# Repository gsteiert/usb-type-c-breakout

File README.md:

# usb-type-c-breakout
USB Type C Breakout Adapter

This board breaks out a USB Type-C plug to pairs of SMA connectors for each of the super speed pairs, a USB micro B connector for D+/-, and an 8 pin header for the rest of the signals.

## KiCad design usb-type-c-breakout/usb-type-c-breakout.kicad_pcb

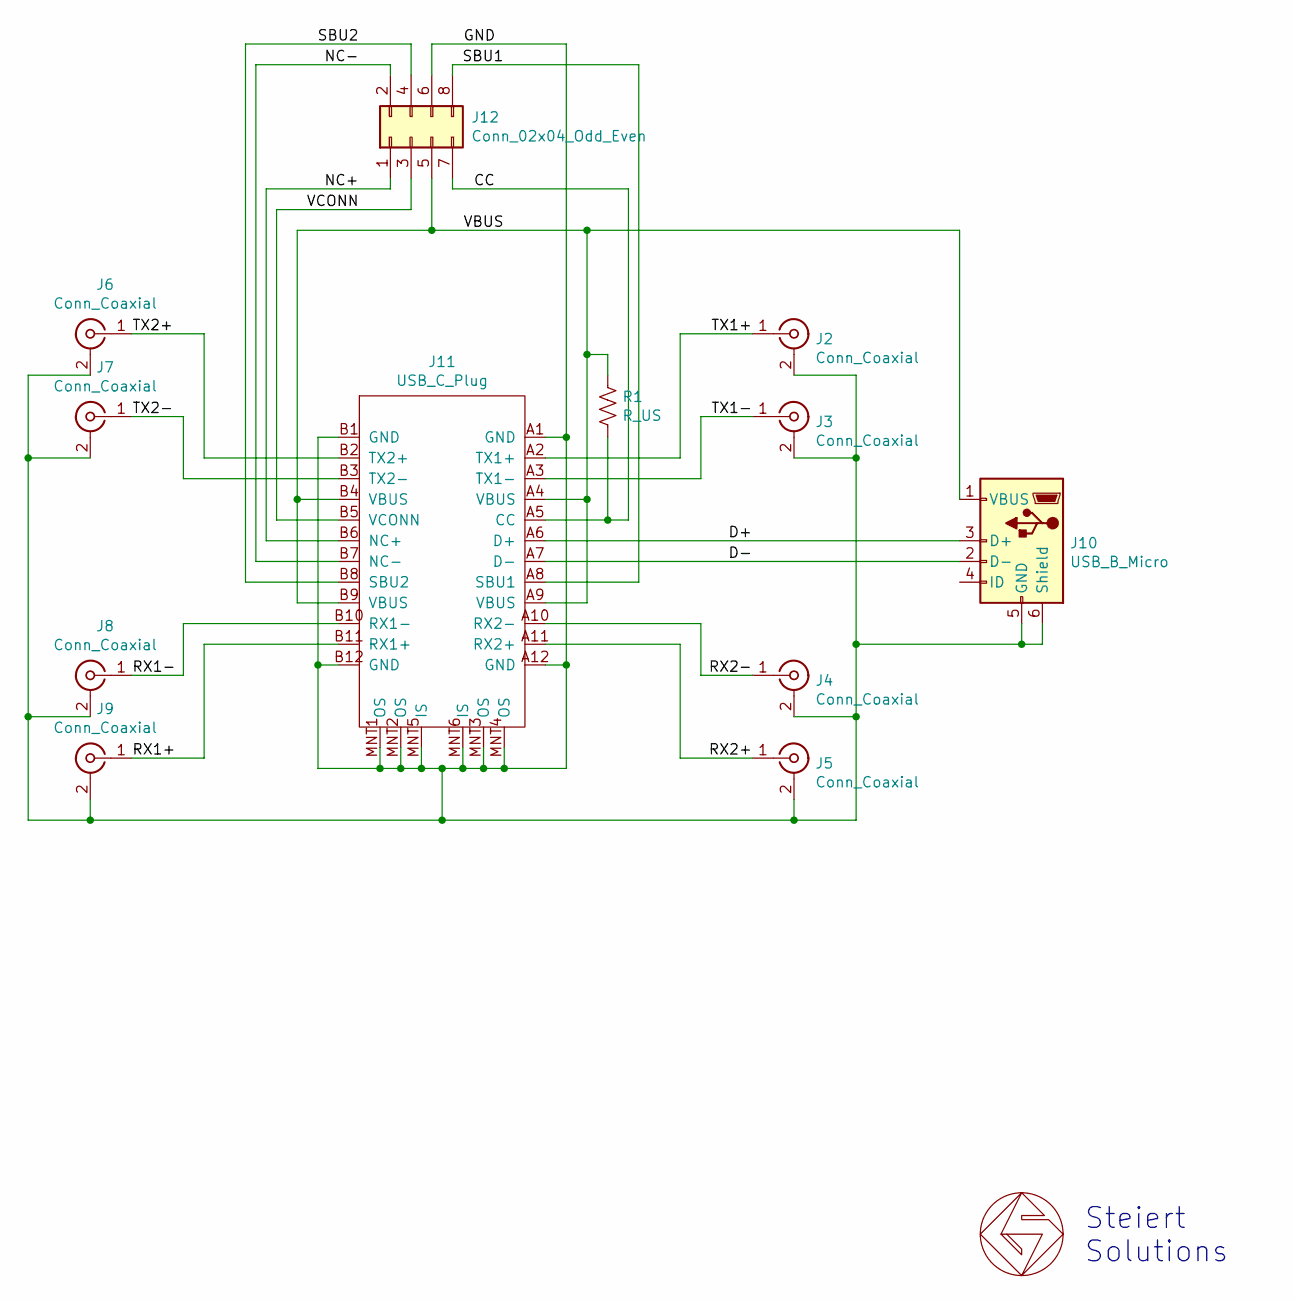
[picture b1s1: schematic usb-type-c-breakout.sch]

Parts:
GS1: GS_logo-custom; gs_logo_200mil
J2, J3, J4, J5, J6, J7, J8, J9: Conn_Coaxial; SMA_Amphenol_132289_EdgeMount; Mouser 223-CON-SMA-EDGE
J10: USB_B_Micro; USB_Micro-B_Wuerth_629105150521; Mouser 710-629105150521
J11: USB_C_Plug; USB_C_Plug_Vertical; Mouser 656-DX07VN24WA2C1568
J12: Conn_02x04_Odd_Even; PinHeader_2x04_P2.54mm_Vertical_SMD; Mouser 649-1012938390801ALF
R1: R_US; R_0603_1608Metric; Mouser 652-CR0603JW-563ELF

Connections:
/CC: J11.A5 (CC), J12.7, R1.2
/D+: J10.3 (D+), J11.A6 (D+)
/D-: J10.2 (D-), J11.A7 (D-)
/GND: J2.2 (Ext), J3.2 (Ext), J4.2 (Ext), J5.2 (Ext), J6.2 (Ext), J7.2 (Ext), J8.2 (Ext), J9.2 (Ext), J10.5 (GND), J10.6 (Shield), J11.A1 (GND), J11.A12 (GND), J11.B1 (GND), J11.B12 (GND), J11.MNT1 (OS), J11.MNT2 (OS), J11.MNT3 (OS), J11.MNT4 (OS), J11.MNT5 (IS), J11.MNT6 (IS), J12.6
/NC+: J11.B6 (NC+), J12.1
/NC-: J11.B7 (NC-), J12.2
/RX1+: J9.1 (In), J11.B11 (RX1+)
/RX1-: J8.1 (In), J11.B10 (RX1-)
/RX2+: J5.1 (In), J11.A11 (RX2+)
/RX2-: J4.1 (In), J11.A10 (RX2-)
/SBU1: J11.A8 (SBU1), J12.8
/SBU2: J11.B8 (SBU2), J12.4
/TX1+: J2.1 (In), J11.A2 (TX1+)
/TX1-: J3.1 (In), J11.A3 (TX1-)
/TX2+: J6.1 (In), J11.B2 (TX2+)
/TX2-: J7.1 (In), J11.B3 (TX2-)
/VBUS: J10.1 (VBUS), J11.A4 (VBUS), J11.A9 (VBUS), J11.B4 (VBUS), J11.B9 (VBUS), J12.5, R1.1
/VCONN: J11.B5 (VCONN), J12.3

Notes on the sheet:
Steiert Solutions

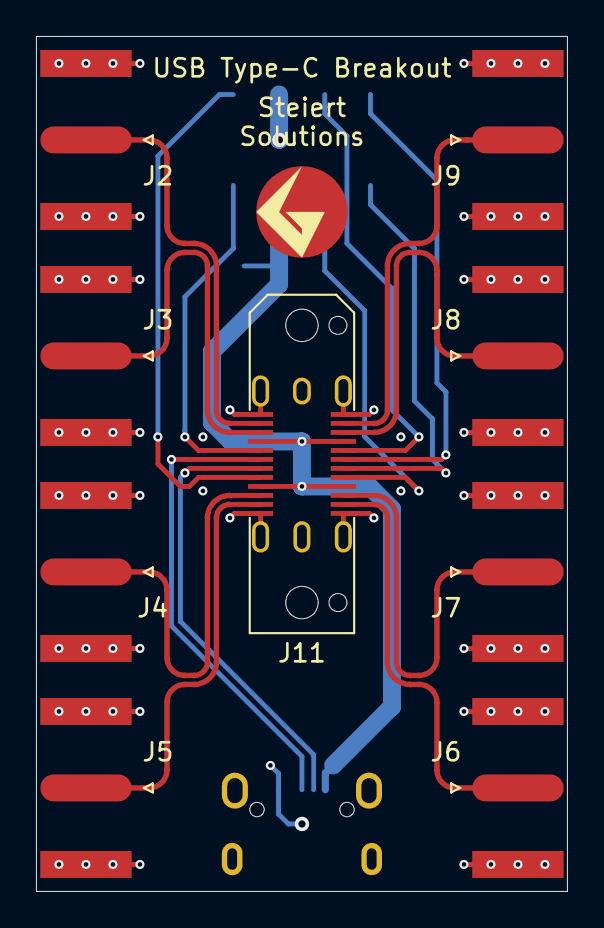
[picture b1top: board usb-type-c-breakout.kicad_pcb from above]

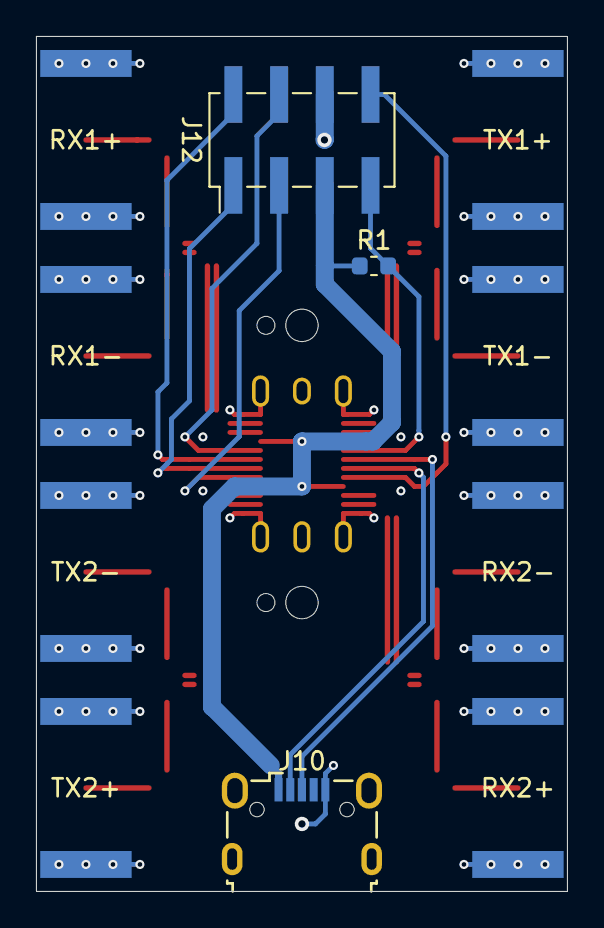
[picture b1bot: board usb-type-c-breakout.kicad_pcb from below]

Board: 4 copper layers, 29.5 x 47.5 mm, 13 parts (3 on the bottom side), 18 nets.

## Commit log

2019-07-14 checking in initial snapshot of design in progress, all components placed
2019-07-14 two example diff pairs routed
2019-07-14 all diff traces routed, pins broken out
2019-07-14 routed USB signals
2019-07-15 fully connected, with poured planes
2019-07-15 added cutouts under SMA signal pad
2019-07-17 assigned curve pads, added silk notes
2019-07-17 updated jpg image
2019-07-17 added plots,pictur,pdf
2020-12-01 cleanup and BOM updates
